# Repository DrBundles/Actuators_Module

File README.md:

# Actuators_Module

# Video Links
- [Materials Part 1](https://ucdenver.hosted.panopto.com/Panopto/Pages/Viewer.aspx?id=055986f1-c3ec-4268-8f4e-aeb30160cd68)
- [Code Day 1 Part 1](https://ucdenver.hosted.panopto.com/Panopto/Pages/Viewer.aspx?id=c7519612-6c13-432e-b2ea-aeb30160e118) 
- [Code Day 1 Part 2](https://ucdenver.hosted.panopto.com/Panopto/Pages/Viewer.aspx?id=c81cfcb9-6042-4e62-9a67-aeb30160f008)
- [Code Day 2 Part 1](https://ucdenver.hosted.panopto.com/Panopto/Pages/Viewer.aspx?id=9c95f3c9-c75f-416a-9927-aeb30160e0f4)
- [Code Day 2 Part 2](https://ucdenver.hosted.panopto.com/Panopto/Pages/Viewer.aspx?id=abec7e0b-8e1e-48be-8ef7-aeb301610b54)
- [Code Day 2 Part 3](https://ucdenver.hosted.panopto.com/Panopto/Pages/Viewer.aspx?id=a6deae2b-6028-43d2-8763-aeb30160e47a)
- [Code Day 3 Part 1](https://ucdenver.hosted.panopto.com/Panopto/Pages/Viewer.aspx?id=0ca2a75e-c111-4d63-9ddc-aeb30160e49d)

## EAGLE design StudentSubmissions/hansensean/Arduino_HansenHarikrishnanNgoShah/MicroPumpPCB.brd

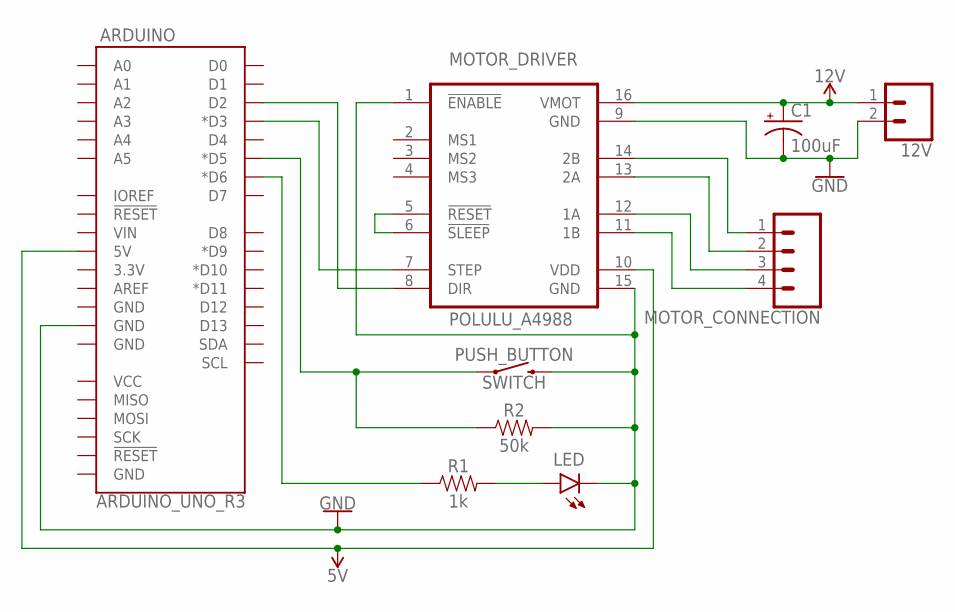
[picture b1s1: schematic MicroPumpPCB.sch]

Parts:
12V: CONN_02POLAR; MOLEX-1X2
ARDUINO: ARDUINO_UNO_R3; ARDUINO_R3
C1: 100uF; CPOL-RADIAL-2.5MM-6.5MM
LED: LED5MM; LED_5MM
MOTOR_CONNECTION: CONN_04; 1X04
POLULU_A4988: MOTOR_DRIVER; POLOLULU2128
PUSH_BUTTON: SWITCH; TACTILE_SWITCH_PTH_6.0MM
R1: 1k; AXIAL-0.3
R2: 50k; AXIAL-0.3

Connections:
5V: ARDUINO.5V, POLULU_A4988.10 (VDD)
12V: 12V.1, C1.1 (+), POLULU_A4988.16 (VMOT)
GND: 12V.2, ARDUINO.GND@3 (GND), C1.2 (-), LED.K (C), POLULU_A4988.1 (!ENABLE), POLULU_A4988.9 (GND), POLULU_A4988.15 (GND), PUSH_BUTTON.3 (2), R2.P$2 (2)
unnamed: ARDUINO.D2, POLULU_A4988.8 (DIR)
unnamed: ARDUINO.D3 (*D3), POLULU_A4988.7 (STEP)
unnamed: MOTOR_CONNECTION.1, POLULU_A4988.14 (2B)
unnamed: MOTOR_CONNECTION.2, POLULU_A4988.13 (2A)
unnamed: MOTOR_CONNECTION.3, POLULU_A4988.12 (1A)
unnamed: MOTOR_CONNECTION.4, POLULU_A4988.11 (1B)
unnamed: ARDUINO.D6 (*D6), R1.P$1 (1)
unnamed: LED.A, R1.P$2 (2)
unnamed: ARDUINO.D5 (*D5), PUSH_BUTTON.1, R2.P$1 (1)
unnamed: POLULU_A4988.5 (!RESET), POLULU_A4988.6 (!SLEEP)

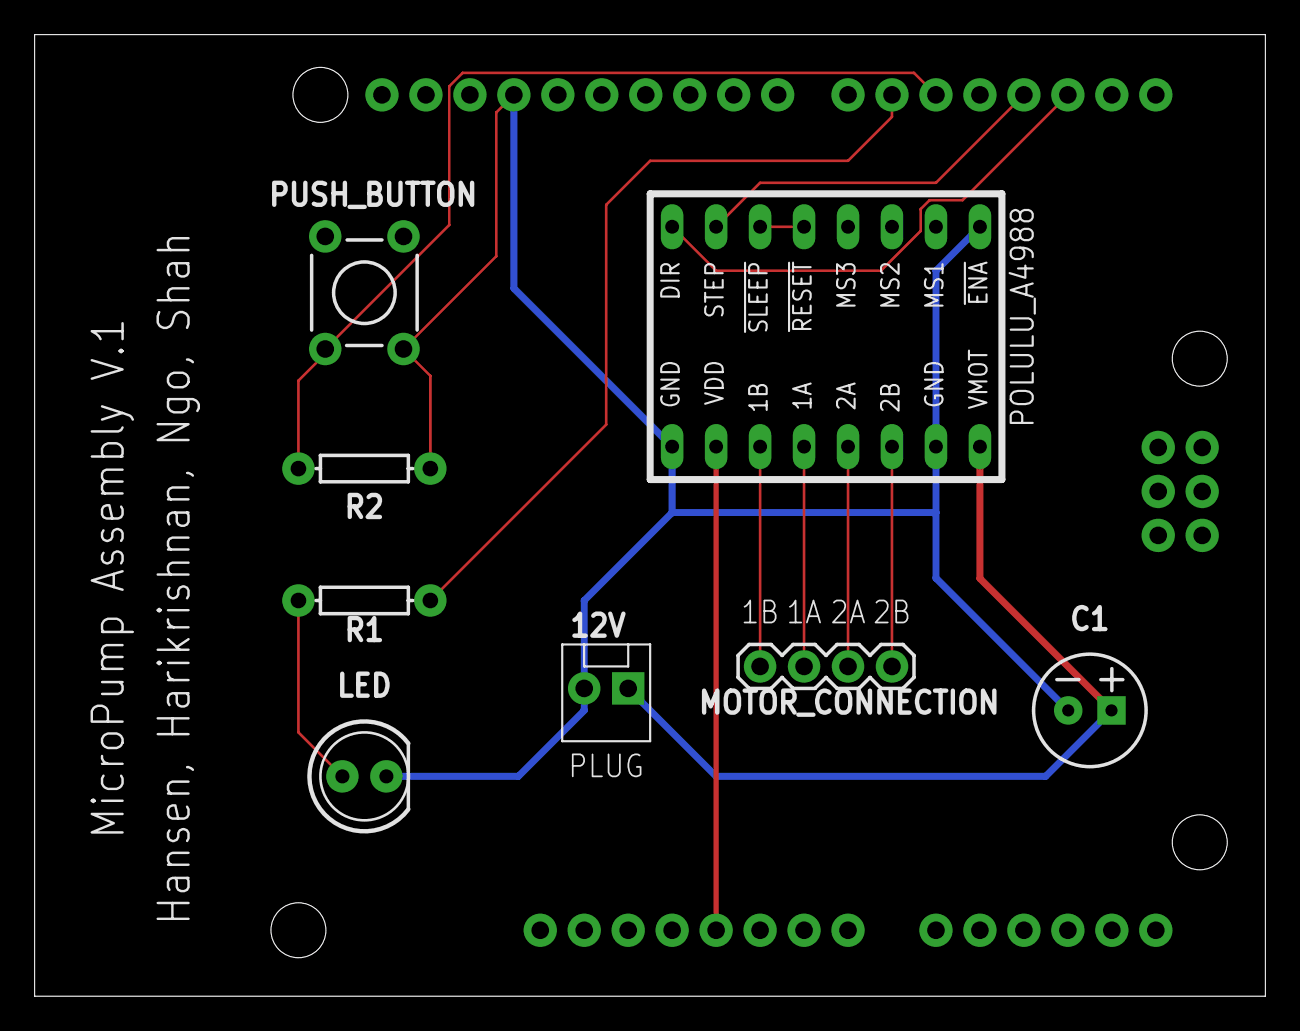
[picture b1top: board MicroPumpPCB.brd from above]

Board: 2 copper layers, 71.1 x 55.5 mm, 9 parts (0 on the bottom side), 13 nets.

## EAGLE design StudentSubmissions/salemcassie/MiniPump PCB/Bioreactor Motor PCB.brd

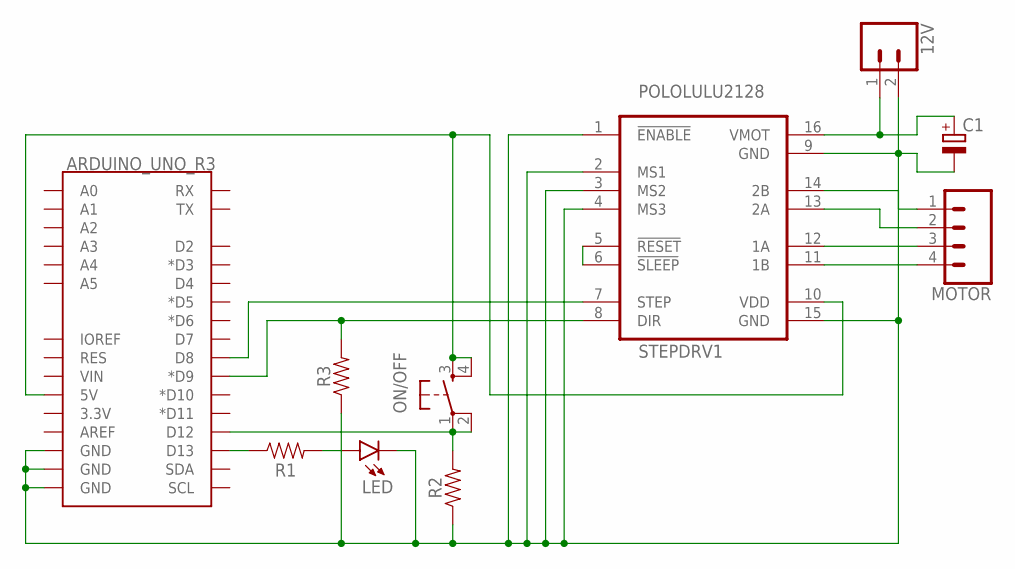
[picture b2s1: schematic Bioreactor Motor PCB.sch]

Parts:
12V: CONN_02POLAR; MOLEX-1X2
ARDUINO_UNO_R3: ARDUINO_UNO_R3_SHIELDBASIC; UNO_R3_SHIELD
C1: CPOL-EUE3.5-8; E3,5-8
LED: TLLG4400; LED3MM
MOTOR: CONN_04POLAR; MOLEX-1X4
ON/OFF: TAC_SWITCHPTH; TACTILE-PTH
R1: 1M; AXIAL-0.3
R2, R3: 1k; AXIAL-0.3
STEPDRV1: POLOLULU2128

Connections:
unnamed: 12V.2, ARDUINO_UNO_R3.GND@0 (GND), ARDUINO_UNO_R3.GND@1 (GND), ARDUINO_UNO_R3.GND@2 (GND), C1.-, LED.K (C), R2.P$1 (1), R3.P$1 (1), STEPDRV1.1 (!ENABLE), STEPDRV1.2 (MS1), STEPDRV1.3 (MS2), STEPDRV1.4 (MS3), STEPDRV1.9 (GND), STEPDRV1.15 (GND)
unnamed: ARDUINO_UNO_R3.D13, R1.P$1 (1)
unnamed: LED.A, R1.P$2 (2)
unnamed: ARDUINO_UNO_R3.D12, ON/OFF.1, ON/OFF.2, R2.P$2 (2)
unnamed: ARDUINO_UNO_R3.5V, ON/OFF.3, ON/OFF.4, STEPDRV1.10 (VDD)
unnamed: 12V.1, C1.+, STEPDRV1.16 (VMOT)
unnamed: STEPDRV1.5 (!RESET), STEPDRV1.6 (!SLEEP)
unnamed: ARDUINO_UNO_R3.D9 (*D9), R3.P$2 (2), STEPDRV1.8 (DIR)
unnamed: ARDUINO_UNO_R3.D8, STEPDRV1.7 (STEP)
unnamed: MOTOR.4, STEPDRV1.11 (1B)
unnamed: MOTOR.3, STEPDRV1.12 (1A)
unnamed: MOTOR.2, STEPDRV1.13 (2A)
unnamed: MOTOR.1, STEPDRV1.14 (2B)

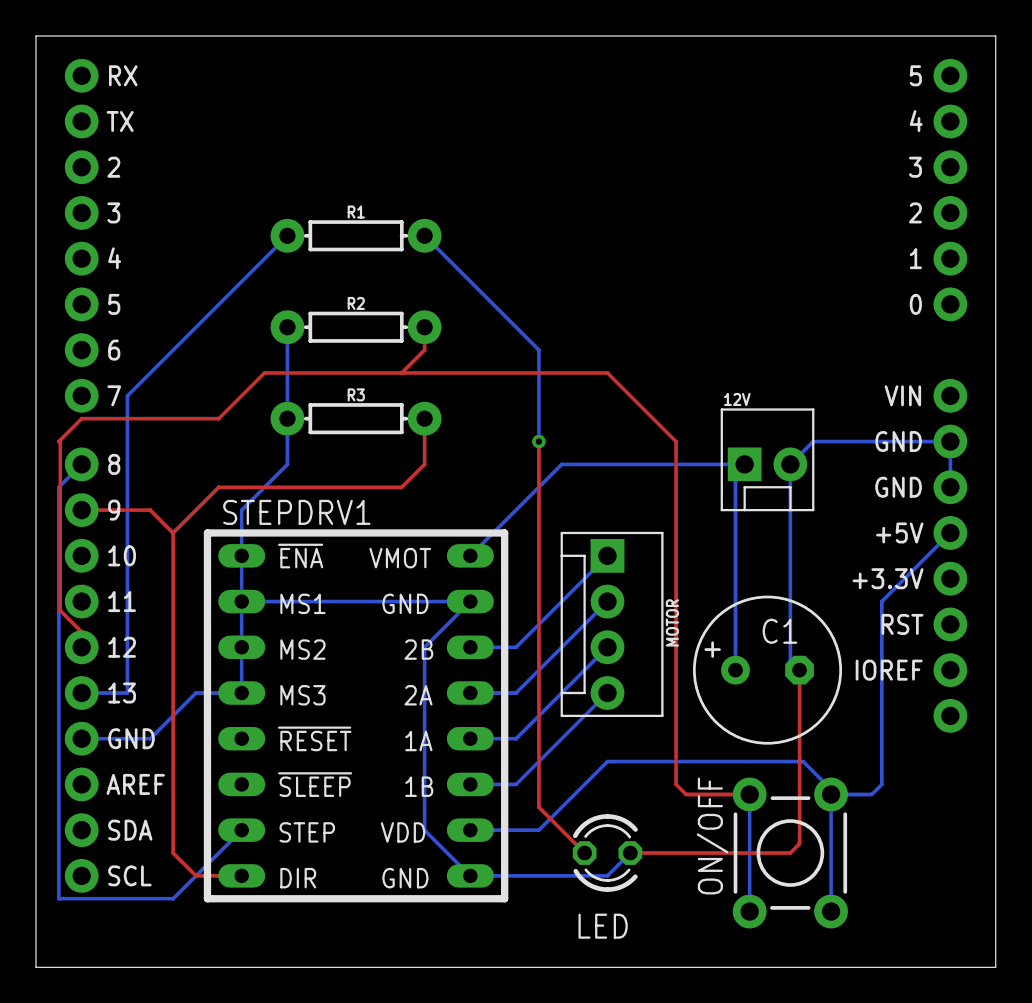
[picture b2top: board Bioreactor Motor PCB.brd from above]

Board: 2 copper layers, 53.3 x 51.7 mm, 10 parts (0 on the bottom side), 13 nets.

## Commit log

2020-02-25 pump added
2023-02-13 general updates

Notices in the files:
parts and their libraries:
SparkFun-Connectors: Licensing: Creative Commons ShareAlike 4.0 International - https://creativecommons.org/licenses/by-sa/4.0
